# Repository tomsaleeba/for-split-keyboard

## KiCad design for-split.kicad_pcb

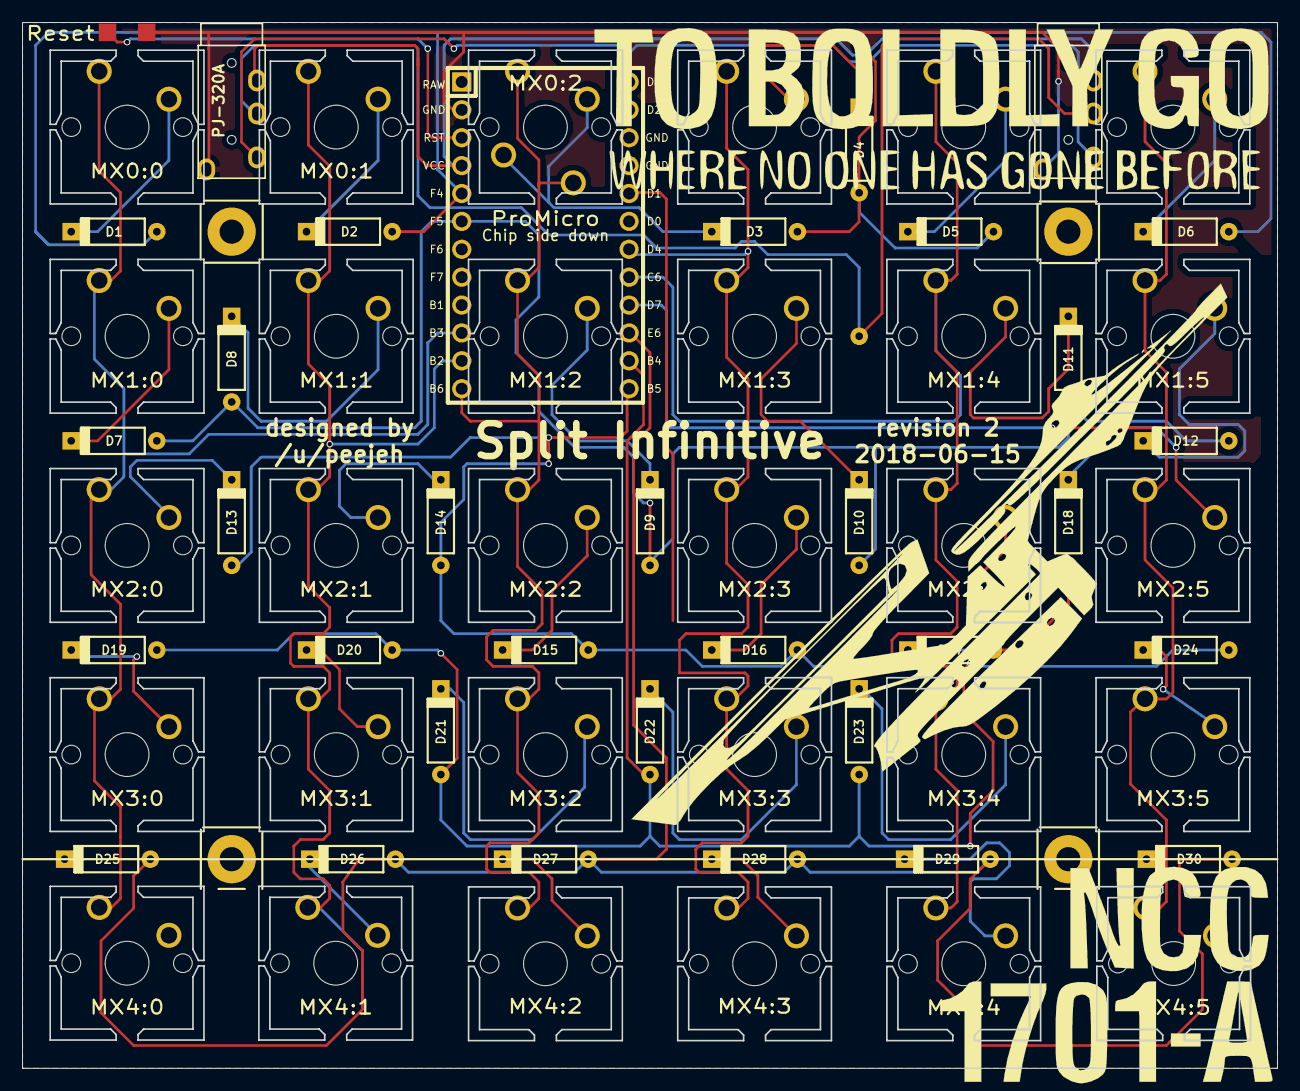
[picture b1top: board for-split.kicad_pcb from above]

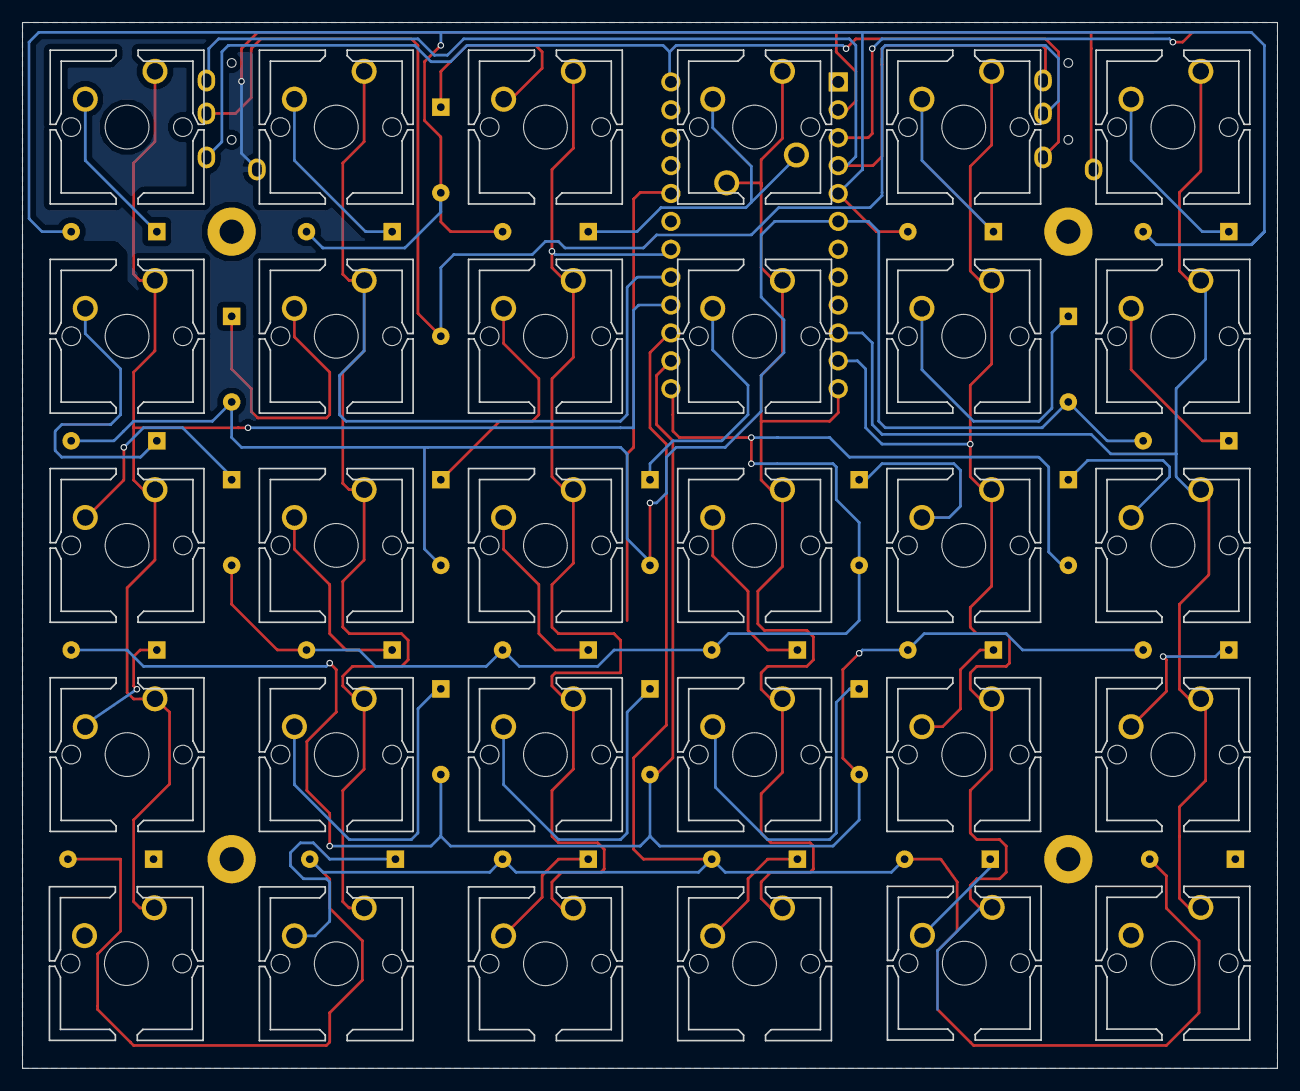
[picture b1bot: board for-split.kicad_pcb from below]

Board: 2 copper layers, 114.3 x 95.2 mm, 70 parts (30 on the bottom side), 42 nets.

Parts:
D1, D2, D3, D4, D5, D6, D7, D8, D9, D10, D11, D12, D13, D14, D15, D16, D17, D18, D19, D20, D21, D22, D23, D24, D25, D26, D27, D28, D29, D30: DIODE
EXTRADATA1: ExtraData; Square_Pad
GROUND1: Ground; Single_Pad
Hole: MountingHole; MountingHole_2.2mm_M2_Pad
Hole#2, Hole#3, Hole#4: MountingHole; MountingHole_2.2mm_M2_Pad
J1, J2: TRRS; PJ-320A
MX0:0: MX0:11; MX_CUTOUT
MX0:1: MX0:10; MX_CUTOUT
MX0:2: MX0:9; MX_CUTOUT_NTHSTH
MX0:3: MX0:8; MX_CUTOUT
MX0:4: MX0:7; MX_CUTOUT
MX0:5: MX0:6; MX_CUTOUT
MX1:0: MX1:11; MX_CUTOUT
MX1:1: MX1:10; MX_CUTOUT
MX1:2: MX1:9; MX_CUTOUT
MX1:3: MX1:8; MX_CUTOUT
MX1:4: MX1:7; MX_CUTOUT
MX1:5: MX1:6; MX_CUTOUT
MX2:0: MX2:11; MX_CUTOUT
MX2:1: MX2:10; MX_CUTOUT
MX2:2: MX2:9; MX_CUTOUT
MX2:3: MX2:8; MX_CUTOUT
MX2:4: MX2:7; MX_CUTOUT
MX2:5: MX2:6; MX_CUTOUT
MX3:0: MX3:11; MX_CUTOUT
MX3:1: MX3:10; MX_CUTOUT
MX3:2: MX3:9; MX_CUTOUT
MX3:3: MX3:8; MX_CUTOUT
MX3:4, MX4:4, MX4:5: MX3:7; MX_CUTOUT
MX3:5: MX3:6; MX_CUTOUT
MX4:0: MX4:11; MX_CUTOUT
MX4:1: MX4:10; MX_CUTOUT
MX4:2: MX4:9; MX_CUTOUT
MX4:3: MX4:8; MX_CUTOUT
RESET1: Reset; Single_Pad
U1: ProMicro; Pro_Micro_ChipSideDown

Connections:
/Col0: MX0:0.1, MX1:0.1, MX2:0.1, MX3:0.1, MX4:0.1, MX4:1.1, U1.10
/Col1: MX0:1.1, MX1:1.1, MX2:1.1, MX3:1.1, U1.11
/Col2: MX0:2.1, MX1:2.1, MX2:2.1, MX3:2.1, MX4:2.1, U1.12
/Col3: MX0:3.1, MX1:3.1, MX2:3.1, MX3:3.1, MX4:3.1, U1.19
/Col4: MX0:4.1, MX1:4.1, MX2:4.1, MX3:4.1, MX4:4.1, MX4:5.1, U1.20
/Col5: MX0:5.1, MX1:5.1, MX2:5.1, MX3:5.1, U1.21
/Data: J1.2, J2.2, U1.13
/Row0: D1.2, D2.2, D3.2, D4.2, D5.2, D6.2, U1.5
/Row1: D7.2, D8.2, D9.2, D10.2, D11.2, D12.2, U1.6
/Row2: D13.2, D14.2, D15.2, D16.2, D17.2, D18.2, U1.24
/Row3: D19.2, D20.2, D21.2, D22.2, D23.2, D24.2, U1.23
/Row4: D25.2, D26.2, D27.2, D28.2, D29.2, D30.2, U1.22
GND: GROUND1.1, J1.1, J2.1, U1.2
unnamed: D1.1, MX0:0.2
unnamed: D2.1, MX0:1.2
unnamed: D3.1, MX0:2.2
unnamed: D4.1, MX0:3.2
unnamed: D5.1, MX0:4.2
unnamed: D6.1, MX0:5.2
unnamed: D7.1, MX1:0.2
unnamed: D8.1, MX1:1.2
unnamed: D9.1, MX1:2.2
unnamed: D10.1, MX1:3.2
unnamed: D11.1, MX1:4.2
unnamed: D12.1, MX1:5.2
unnamed: D13.1, MX2:0.2
unnamed: D14.1, MX2:1.2
unnamed: D15.1, MX2:2.2
unnamed: D16.1, MX2:3.2
unnamed: D17.1, MX2:4.2
unnamed: D18.1, MX2:5.2
unnamed: D19.1, MX3:0.2, MX4:0.2, MX4:1.2
unnamed: D20.1, MX3:1.2
unnamed: D21.1, MX3:2.2
unnamed: D22.1, MX3:3.2
unnamed: D23.1, MX3:4.2, MX4:4.2, MX4:5.2
unnamed: D24.1, MX3:5.2
unnamed: D27.1, MX4:2.2
unnamed: D28.1, MX4:3.2
unnamed: EXTRADATA1.1, J1.3, J2.3
unnamed: RESET1.1, U1.3
VCC: J1.4, J2.4, U1.4

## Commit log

2019-10-26 chore: removed 2U switches and edge connections, missing traces on switches because I think nets are munged
